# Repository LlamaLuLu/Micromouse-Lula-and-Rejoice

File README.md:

# 🐭 Micromouse Power Subsystem – EEE3088F 2025

> A modular and cost-efficient power subsystem designed for the Micromouse platform, focusing on power delivery, battery management, voltage regulation, and motor control.  
> 🔧 Built to integrate with a shared motherboard using a 2×16 pin header.

---

## 📐 Design Requirements

- Must interface with **shared motherboard via 2×16 pin header**
- All subsystems must **interoperate safely and reliably**
- Total cost must not exceed **$28.25 per student**
- Designed with **PCB production in mind** (JLCPCB compatible)

---

## ⚡ Subsystems Overview

### 1. USB-C Power Input
- **Objective**: Extract and regulate power from USB-C
- **Default Output**: 5V  
- **Target Output**: 9V
- **Approaches**:
  - Step-up converter (boost from 5V)
  - Request 9V from port using USB PD (Power Delivery) negotiation

### 2. Battery Management
- **Battery**: 3.7V 800mAh LiPo (used in micro robotics)
- **Charging Input**: 9V (from USB-C)
- **Charging Modes**:
  - Low current: **200mA**
  - High current: **(600 ± 100)mA**
- **Key Considerations**:
  - LiPo is **sensitive to overcharging**
- **Design Strategies**:
  - Use a **battery management IC**
  - Dual-mode charging circuit (selectable)
    - Separate high- and low-current paths
  - OR: Current regulation on USB-C input side that supports both modes

### 3. Power Switching & Regulation

#### 🔌 Power Switch
- Enables/disables battery output to downstream circuits

#### 🔋 Voltage Regulation
- Battery output can supply up to **400mA**
- **Approach**: Efficient voltage regulation using buck converters
- **Protection**: Optional current amplification for regulated rails

#### 🔀 External Load Switching
- Must control **2 external loads**, each up to **1A**
- **Solution**: High-current **MOSFET switching circuits**
- Current path design considers **external load values**

### 4. Components & Motor Drivers

#### 🔍 Current Sensor
- **INA219** or similar  
- Connects via **I²C**  
- Placed on high-side battery line for real-time monitoring

#### 🚗 Motor Control
- **Primary Motors**: 2 × 200mA  
- **Auxiliary Motors**: 2 × 500mA  
- Control via **dual H-bridge** motor driver (e.g., DRV8833)
- Motors driven bidirectionally using **PWM from MCU**

---

## 🧰 Production & Submission Instructions (EEE3088F)

The final PCB submission is in a zipped folder:
[Final PCB Files](./EEE3088F_PCB_Project/jlcpcb/production_files/EEE3088F_2025_Project_PCB_Files_Group_66_LNGLUL002_MTMREJ003.zip)

_ZIP File Includes:_
1. Zipped **Gerber** files (with silkscreen including group & student numbers)
2. **BOM `.csv`** file  
3. **POS/CPL `.csv`** file  
4. Screenshot of **JLCPCB BOM upload** page  
5. Screenshot of **JLCPCB Add to Cart** confirmation page  

📷 PCB Design:
- Schematic

- PCB Wiring

- JLCPCB Design (Front)

- JLCPCB Design (Back)

---

## 👨‍💻 Authors: Group 66

- **Lulama Lingela** (LNGLUL002)
- **Rejoice Matema** (MTMREJ003)

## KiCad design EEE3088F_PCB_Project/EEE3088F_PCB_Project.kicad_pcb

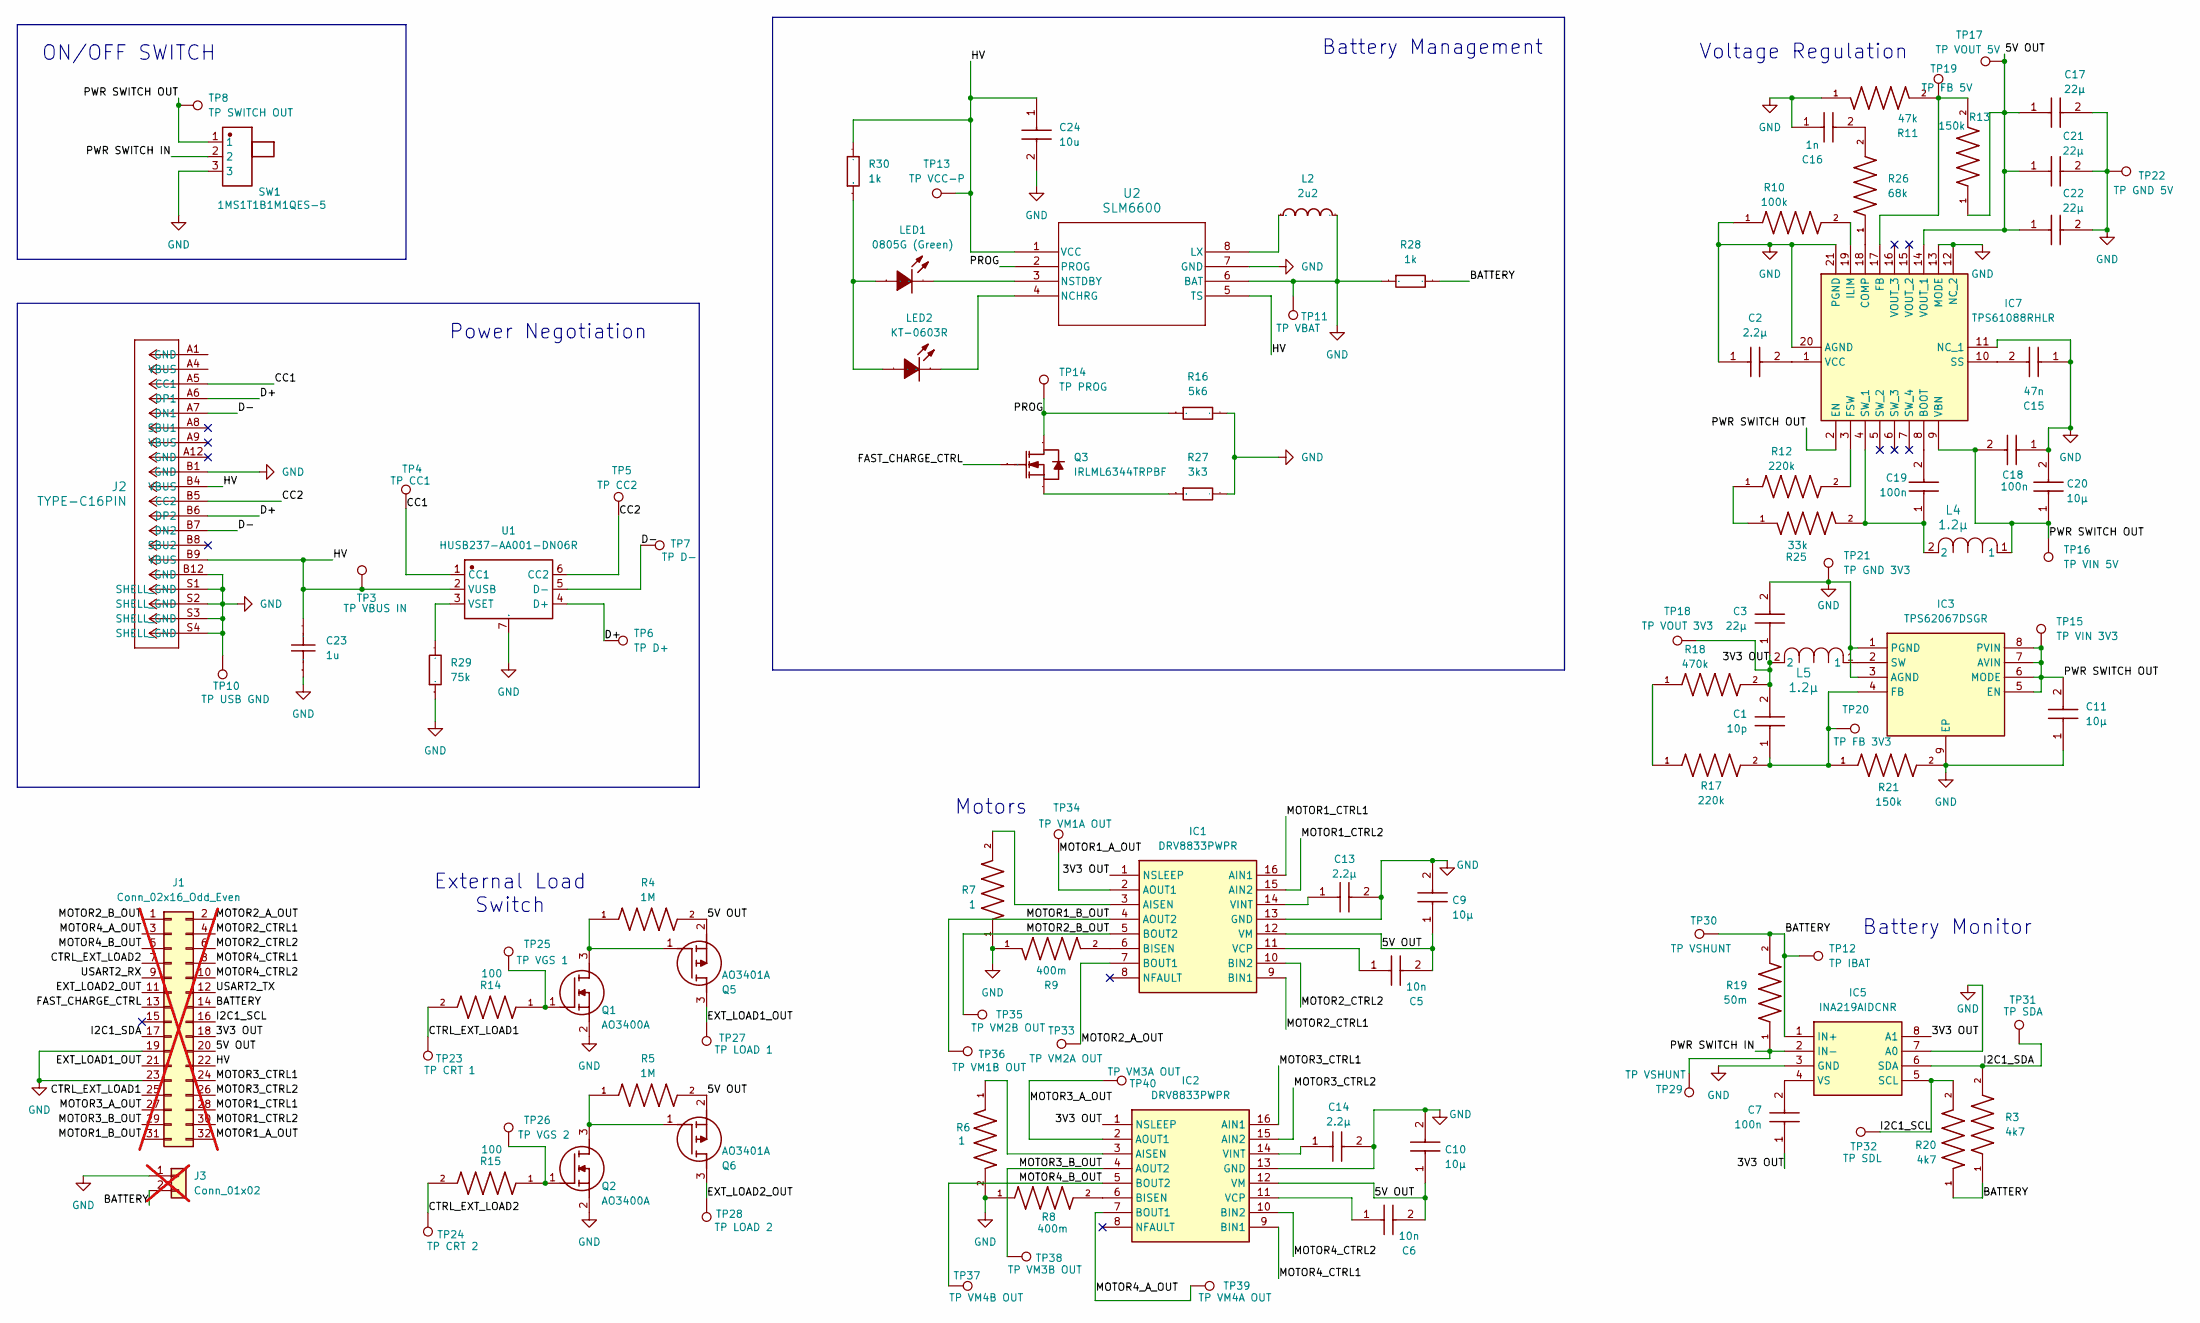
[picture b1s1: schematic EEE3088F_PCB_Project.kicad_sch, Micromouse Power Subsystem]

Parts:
C1: 10p; CAPC1608X90N; Manufacturer_Part_Number CL10C100JB8NNNC; Mouser Part Number 187-CL10C100JB8NNNC
C2, C13, C14: 2.2µ; CAPC3216X180N; Manufacturer_Part_Number CL31B225KBHNNNE; Mouser Part Number 187-CL31B225KBHNNNE
C3: 22µ; CAPC2012X140N; Manufacturer_Part_Number CL21A226MAQNNNE; Mouser Part Number 187-CL21A226MAQNNNE
C5, C6: 10n; CAPC2012X75N; Manufacturer_Part_Number CL21B103KBANNNC; Mouser Part Number 187-CL21B103KBANNNC
C7, C18, C19: 100n; CAPC3216X100N; Manufacturer_Part_Number CL31B104KBCNNNC; Mouser Part Number 187-CL31B104KBCNNNC
C9, C10, C11, C20: 10µ; CAPC3216X180N; Manufacturer_Part_Number CL31A106KBHNNNE; Mouser Part Number 187-CL31A106KBHNNNE
C15: 47n; CAPC1608X90N; Manufacturer_Part_Number CL10B473KB8NNNC; Mouser Part Number 187-CL10B473KB8NNNC
C16: 1n; CAPC3215X163N; Manufacturer_Part_Number 1206B102K202NT; Mouser Part Number 767-1206B102K202NT
C17, C21, C22: 22µ; CAPC2012X140N; Manufacturer_Part_Number CL31A226KAHNNNE; Mouser Part Number 187-CL31A226KAHNNNE
C23: 1u; C1206; Manufacturer Part CL31B105KBHNNNE; LCSC C1848
C24: 10u; CAPC3216X180N; Manufacturer_Part_Number CL31A106KBHNNNE; Mouser Part Number 187-CL31A106KBHNNNE
IC1, IC2: DRV8833PWPR; SOP65P640X120-16N; Manufacturer_Part_Number DRV8833PWPR; Mouser Part Number 595-DRV8833PWPR
IC3: TPS62067DSGR; SON50P200X200X80-9N; Manufacturer_Part_Number TPS62067DSGR; Mouser Part Number 595-TPS62067DSGR
IC5: INA219AIDCNR; SOP65P280X145-8N; Manufacturer_Part_Number INA219AIDCNR; Mouser Part Number 595-INA219AIDCNR
IC7: TPS61088RHLR; RHL_R-PVQFN-N20__1; Manufacturer_Part_Number TPS61088RHLR; Mouser Part Number 595-TPS61088RHLR
J1: Conn_02x16_Odd_Even; PinSocket_2x16_P2.54mm_Vertical; not fitted
J2: TYPE-C16PIN; CONN16_C16PIN_SHN; LCSC C393939
J3: Conn_01x02; JST_PH_S2B-PH-K_1x02_P2.00mm_Horizontal; not fitted
L2: 2u2; L0805; Manufacturer Part FHW0805UF2R2JST; LCSC C41651
L4, L5: 1.2µ; IND_FXL0420_CMT; LCSC C167204
LED1: 0805G (Green); LED0805-R-RD; Manufacturer Part KT-0805G; LCSC C2297
LED2: KT-0603R; LED0603-RD; Manufacturer Part KT-0603R; LCSC C2286
Q1, Q2: AO3400A; SOT95P280X125-3N; Manufacturer_Part_Number AO3400A; LCSC C20917
Q3: IRLML6344TRPBF; IRLML6344TRPBF_INF; Manufacturer Part IRLML6344TRPBF; LCSC C53550
Q5, Q6: AO3401A; SOT95P280X125-3N; Manufacturer_Part_Number AO3401A; LCSC C15127
R3, R20: 4k7; RESC3115X65N; PARTREV V3; LCSC C17936
R4, R5: 1M; RESC3115X65N; PARTREV V3; LCSC C17927
R6, R7: 1; RESC3115X65N; PARTREV V3; LCSC C17928
R8, R9: 400m; RESC3115X65N; PARTREV V3; LCSC C247521
R10: 100k; RESC3115X65N; PARTREV V3; LCSC C17900
R11: 47k; RESC2012X65N; PARTREV V3; LCSC C17713
R12, R17: 220k; RESC2012X65N; PARTREV V3; LCSC C17556
R13, R21: 150k; RESC2012X65N; PARTREV V3; LCSC C17470
R14, R15: 100; RESC3115X65N; PARTREV V3; LCSC C17901
R16: 5k6; R0402; Manufacturer Part 0402WGF5601TCE; LCSC C25908
R18: 470k; RESC2012X65N; PARTREV V3; LCSC C17709
R19: 50m; RESC3115X65N; PARTREV V3; LCSC C127691
R25: 33k; RESC2012X65N; PARTREV V3; LCSC C17633
R26: 68k; RESC2012X65N; PARTREV V3; LCSC C17801
R27: 3k3; R0402; Manufacturer Part 0402WGF3301TCE; LCSC C25890
R28, R30: 1k; R0402; Manufacturer Part 0402WGF1001TCE; LCSC C11702
R29: 75k; R0603; Manufacturer Part 0603WAF7502T5E; LCSC C23242
SW1: 1MS1T1B1M1QES-5; SW-TH_1MS1T1B1M1QES-5; Manufacturer Part 1MS1T1B1M1QES-5; LCSC C496154
TP3: TP VBUS IN; TestPoint_Pad_D1.5mm
TP4: TP CC1; TestPoint_Pad_D1.5mm
TP5: TP CC2; TestPoint_Pad_D1.5mm
TP6: TP D+; TestPoint_Pad_D1.5mm
TP7: TP D-; TestPoint_Pad_D1.5mm
TP8: TP SWITCH OUT; TestPoint_Pad_D1.5mm
TP10: TP USB GND; TestPoint_Pad_D1.5mm
TP11: TP VBAT; TestPoint_Pad_D1.5mm
TP12: TP IBAT; TestPoint_Pad_D1.5mm
TP13: TP VCC-P; TestPoint_Pad_D1.5mm
TP14: TP PROG; TestPoint_Pad_D1.5mm
TP15: TP VIN 3V3; TestPoint_Pad_D1.5mm
TP16: TP VIN 5V; TestPoint_Pad_D1.5mm
TP17: TP VOUT 5V; TestPoint_Pad_D1.5mm
TP18: TP VOUT 3V3; TestPoint_Pad_D1.5mm
TP19: TP FB 5V; TestPoint_Pad_D1.5mm
TP20: TP FB 3V3; TestPoint_Pad_D1.5mm
TP21: TP GND 3V3; TestPoint_Pad_D1.5mm
TP22: TP GND 5V; TestPoint_Pad_D1.5mm
TP23: TP CRT 1; TestPoint_Pad_D1.5mm
TP24: TP CRT 2; TestPoint_Pad_D1.5mm
TP25: TP VGS 1; TestPoint_Pad_D1.5mm
TP26: TP VGS 2; TestPoint_Pad_D1.5mm
TP27: TP LOAD 1; TestPoint_Pad_D1.5mm
TP28: TP LOAD 2; TestPoint_Pad_D1.5mm
TP29, TP30: TP VSHUNT; TestPoint_Pad_D1.5mm
TP31: TP SDA; TestPoint_Pad_D1.5mm
TP32: TP SDL; TestPoint_Pad_D1.5mm
TP33: TP VM2A OUT; TestPoint_Pad_D1.5mm
TP34: TP VM1A OUT; TestPoint_Pad_D1.5mm
TP35: TP VM2B OUT; TestPoint_Pad_D1.5mm
TP36: TP VM1B OUT; TestPoint_Pad_D1.5mm
TP37: TP VM4B OUT; TestPoint_Pad_D1.5mm
TP38: TP VM3B OUT; TestPoint_Pad_D1.5mm
TP39: TP VM4A OUT; TestPoint_Pad_D1.5mm
TP40: TP VM3A OUT; TestPoint_Pad_D1.5mm
U1: HUSB237-AA001-DN06R; TDFN-6_L2.0-W2.0-P0.65-TL-EP; Manufacturer Part HUSB237-AA001-DN06R; LCSC C22373734
U2: SLM6600; SOP8_4X5P1-1P27_SOI; LCSC C130316

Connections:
/3V3 OUT: C1.2, C3.1, C7.1, IC1.1 (NSLEEP), IC2.1 (NSLEEP), IC5.8 (A1), J1.18, L5.2, R18.2, TP18.1
/5V OUT: C5.2, C6.2, C9.1, C10.1, C17.1, C21.1, C22.1, IC1.12 (VM), IC2.12 (VM), IC7.14 (VOUT_1), J1.20, Q5.2 (S), Q6.2 (S), R4.2, R5.2, R13.1, TP17.1
/BATTERY: IC5.1 (IN+), J1.14, J3.2, R3.1, R19.2, R20.1, R28.2, TP12.1, TP30.1
/CC1: J2.A5 (CC1), TP4.1, U1.1 (CC1)
/CC2: J2.B5 (CC2), TP5.1, U1.6 (CC2)
/CTRL_EXT_LOAD1: J1.25, R14.2, TP23.1
/CTRL_EXT_LOAD2: J1.7, R15.2, TP24.1
/D+: J2.A6 (DP1), J2.B6 (DP2), TP6.1, U1.4 (D+)
/D-: J2.A7 (DN1), J2.B7 (DN2), TP7.1, U1.5 (D-)
/EXT_LOAD1_OUT: J1.21, Q5.3 (D), TP27.1
/EXT_LOAD2_OUT: J1.11, Q6.3 (D), TP28.1
/FAST_CHARGE_CTRL: J1.13, Q3.1 (G)
/HV: C23.2, C24.1, J1.22, J2.B4 (VBUS), J2.B9 (VBUS), R30.2, TP3.1, TP13.1, U1.2 (VUSB), U2.1 (VCC), U2.5 (TS)
/I2C1_SCL: IC5.5 (SCL), J1.16, R20.2, TP32.1
/I2C1_SDA: IC5.6 (SDA), J1.17, R3.2, TP31.1
/MOTOR1_A_OUT: IC1.2 (AOUT1), J1.32, TP34.1
/MOTOR1_B_OUT: IC1.4 (AOUT2), J1.31, TP36.1
/MOTOR1_CTRL1: IC1.16 (AIN1), J1.28
/MOTOR1_CTRL2: IC1.15 (AIN2), J1.30
/MOTOR2_A_OUT: IC1.7 (BOUT1), J1.2, TP33.1
/MOTOR2_B_OUT: IC1.5 (BOUT2), J1.1, TP35.1
/MOTOR2_CTRL1: IC1.9 (BIN1), J1.4
/MOTOR2_CTRL2: IC1.10 (BIN2), J1.6
/MOTOR3_A_OUT: IC2.2 (AOUT1), J1.27, TP40.1
/MOTOR3_B_OUT: IC2.4 (AOUT2), J1.29, TP38.1
/MOTOR3_CTRL1: IC2.16 (AIN1), J1.24
/MOTOR3_CTRL2: IC2.15 (AIN2), J1.26
/MOTOR4_A_OUT: IC2.7 (BOUT1), J1.3, TP39.1
/MOTOR4_B_OUT: IC2.5 (BOUT2), J1.5, TP37.1
/MOTOR4_CTRL1: IC2.9 (BIN1), J1.8
/MOTOR4_CTRL2: IC2.10 (BIN2), J1.10
/PROG: Q3.3 (D), R16.1, TP14.1, U2.2 (PROG)
/PWR SWITCH IN: IC5.2 (IN-), R19.1, SW1.2, TP29.1
/PWR SWITCH OUT: C11.2, C18.2, C20.1, IC3.5 (EN), IC3.6 (MODE), IC3.7 (AVIN), IC3.8 (PVIN), IC7.2 (EN), IC7.9 (VBN), L4.1, SW1.1, TP8.1, TP15.1, TP16.1
/USART2_RX: J1.9
/USART2_TX: J1.12
GND: C2.1, C3.2, C9.2, C10.2, C11.1, C13.2, C14.2, C15.1, C16.1, C17.2, C18.1, C20.2, C21.2, C22.2, C23.1, C24.2, IC1.13 (GND), IC2.13 (GND), IC3.1 (PGND), IC3.3 (AGND), IC3.9 (EP), IC5.3 (GND), IC5.7 (A0), IC7.11 (NC_1), IC7.12 (NC_2), IC7.13 (MODE), IC7.20 (AGND), IC7.21 (PGND), J1.19, J1.23, J2.B1 (GND), J2.B12 (GND), J2.S1 (SHELL_GND), J2.S2 (SHELL_GND), J2.S3 (SHELL_GND), J2.S4 (SHELL_GND), J3.1, L2.2, Q1.2 (S), Q2.2 (S), R6.2, R7.1, R8.1, R9.1, R10.1, R11.1, R16.2, R21.2, R27.2, R28.1, R29.1, SW1.3, TP10.1, TP11.1, TP21.1, TP22.1, U1.7 (GND), U2.6 (BAT), U2.7 (GND); also elsewhere on the board
unnamed: C16.2, R26.2
unnamed: IC1.3 (AISEN), R7.2
unnamed: IC1.6 (BISEN), R9.2
unnamed: C5.1, IC1.11 (VCP)
unnamed: C13.1, IC1.14 (VINT)
unnamed: IC2.3 (AISEN), R6.1
unnamed: IC2.6 (BISEN), R8.2
unnamed: C6.1, IC2.11 (VCP)
unnamed: C14.1, IC2.14 (VINT)
unnamed: C1.1, IC3.4 (FB), R17.2, R21.1, TP20.1
unnamed: IC3.2 (SW), L5.1
unnamed: C7.2, IC5.4 (VS)
unnamed: C19.2, IC7.8 (BOOT)
unnamed: IC7.18 (COMP), R26.1
unnamed: IC7.17 (FB), R11.2, R13.2, TP19.1
unnamed: IC7.3 (FSW), R12.2
unnamed: IC7.19 (ILIM), R10.2
unnamed: C15.2, IC7.10 (SS)
unnamed: C19.1, IC7.4 (SW_1), L4.2, R25.2
unnamed: C2.2, IC7.1 (VCC)
unnamed: LED1.1 (A), LED2.2 (A), R30.1
unnamed: LED1.2 (K), U2.3 (NSTDBY)
unnamed: LED2.1 (K), U2.4 (NCHRG)
unnamed: Q1.3 (D), Q5.1 (G), R4.1
unnamed: Q1.1 (G), R14.1, TP25.1
unnamed: Q2.3 (D), Q6.1 (G), R5.1
unnamed: Q2.1 (G), R15.1, TP26.1
unnamed: Q3.2 (S), R27.1
unnamed: R12.1, R25.1
unnamed: R17.1, R18.1
unnamed: R29.2, U1.3 (VSET)
unnamed: L2.1, U2.8 (LX)

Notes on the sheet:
Motors
Voltage Regulation
Battery Monitor
Battery Management
Power Negotiation
External Load Switch
ON/OFF SWITCH

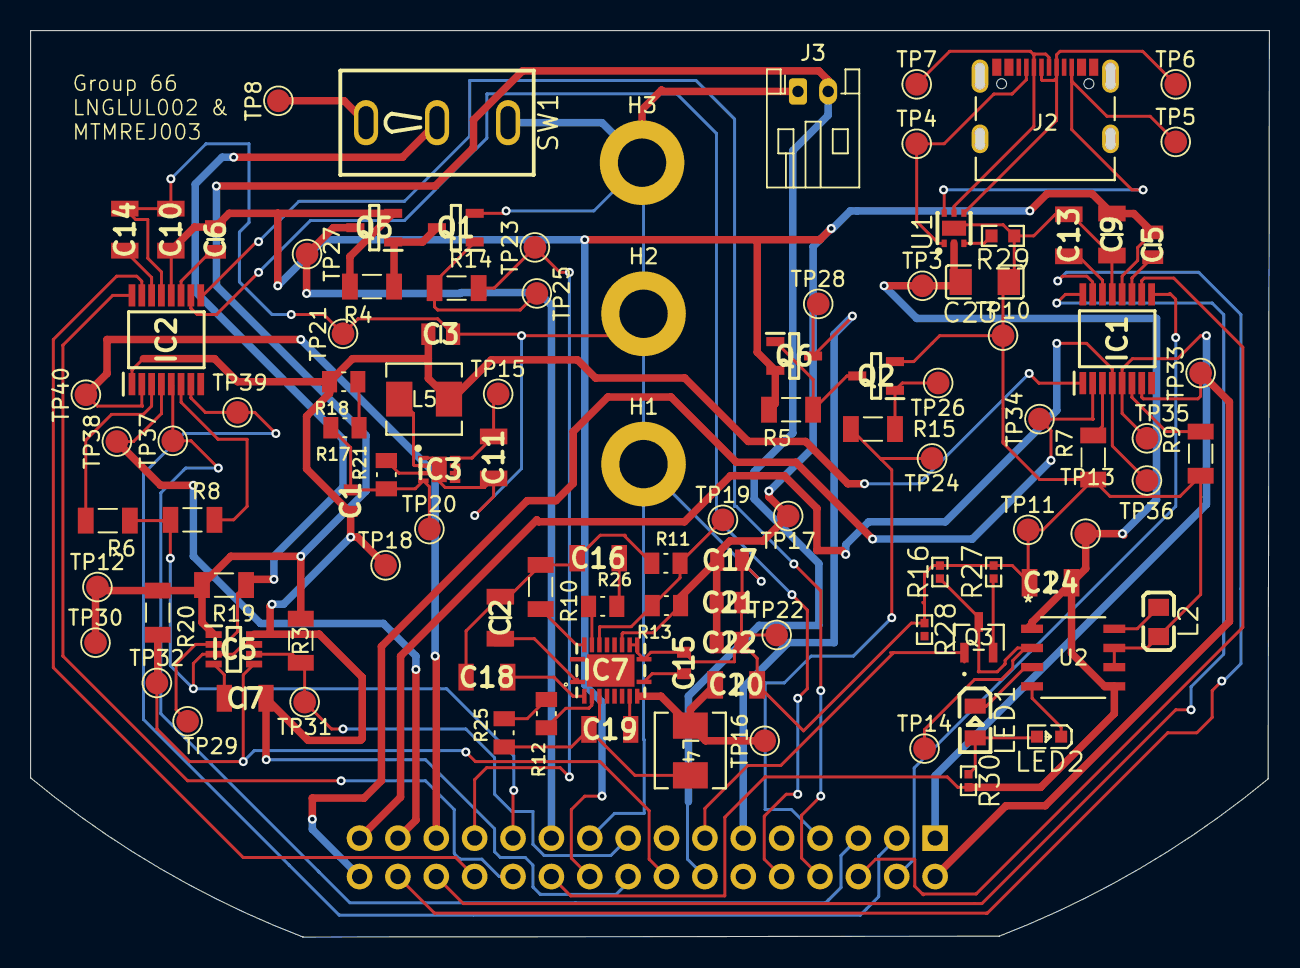
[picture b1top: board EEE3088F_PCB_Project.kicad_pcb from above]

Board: 2 copper layers, 81.4 x 59.4 mm, 107 parts (1 on the bottom side), 67 nets.

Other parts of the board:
H1, H2, H3: MountingHole_3.2mm_M3_DIN965_Pad

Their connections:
GND: H1.1, H2.1, H3.1; also elsewhere on the board

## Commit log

2025-03-24 v0
    KiCad project set up
2025-03-24 v0.1
    Lula: Essential components for my requirements imported to KiCad
2025-03-24 v0.1.1
    Lula: Rearranged position of components to make space for others
2025-03-24 v0.1.2
    Lula: Updated ICs with more compact symbols from Component Search Engine
2025-03-24 v0.1.3
    Lula: Deleted old IC file
2025-03-25 v0.1.4
    Lula: added battery datasheet
2025-03-25 v0.2
    Lula: rough battery monitor circuit done
2025-03-25 v0.2.1
    Lula: Making progress with Motor cct
2025-03-25 v0.3
    Lula: rough schematic for motors done
2025-03-25 v0.3.1
    Lula: datasheets added
2025-03-25 v0.4
    Lula: rough voltage regulator circuits done but bias resistor values not calculated
2025-03-26 v0.5
    Lula: all my rough circuits done
2025-03-26 v0.6
    Lula:
    - motors done
    - some pcb footprints added
    - imports updated
2025-03-26 v0.6.1
    Lula: starting to update battery monitor circuit
2025-03-27 v0.6.2
    Lula: all battery monitor components imported
2025-03-27 v0.6.3
    Lula: external load switch cct updated
2025-03-27 v0.7
    Lula:
    - starting with new voltage regulation cct
    - all other components updated
2025-03-27 v0.7.1
    I put another FUB file cause I saw yours late lol
2025-03-27 v0.7.2
    Lula: moved some circuits out of the way
2025-03-27 v0.7.3
    Removed the newer FUB file. Added Type-C and Im blah blah blah (Toggle Switch)
2025-03-27 v0.7.4
    Removed all my components and put updated files of them instead (FUB, SLM, 1MS, TYPE-C)
2025-03-27 v0.7.5
    Removed Type-C again and added another Type-C and IRLM
2025-03-27 v0.7.6
    Edit for previous updates: Added some components to KiCad.
    Changed some names of my sym files and added components to KiCad
2025-03-27 v0.7.7
    I have my components on the sheet. That's all I remember right now lol
2025-03-28 v0.8
    - updated voltage regulation circuit (still adjusting component values)
2025-03-28 v0.8.1
    Voltage regulator components updated
2025-03-28 v0.8.2
    Added another component
2025-03-28 v0.8.3
    A lot of stuff happened
2025-03-28 Revert "v0.8.3"
    This reverts commit e022e12157d8067f7fb354b48d193a9b7dd025b4.
2025-03-28 v0.9
    Created my circuits in KiCad
2025-03-28 v1.0
    Changed V-REG to PWR SWITCH OUT
2025-03-28 v1.1
    All circuit schematics done
2025-03-28 v1.1.1
    Making sure all changes saved
2025-03-28 v1.2
    Starting with PCB design
2025-03-28 v1.2.1
    Added the rest of my component files to the Imported Components
2025-03-28 v1.2.2
    Footprints added
2025-03-28 v1.3
    Lula: all my footprints imported and circuits grouped on PCB
2025-03-28 v1.3.1
    Most components placed on PCB
2025-03-28 v1.3.2
    Added test points to my parts of the circuit (and some)
2025-03-28 V1.3.3
    Added test points to my parts of the circuit
2025-03-28 v1.3.4
    test points added
2025-03-28 V1.4
    FAILED
2025-03-28 Revert "V1.4"
    This reverts commit e5222738783ebac659cce19e32834096aa7270f5.
2025-03-28 Revert "v1.3.4"
    This reverts commit 31f4348740902cc06db09578befa2d9091b6bdd9.
2025-03-28 Revert "V1.3.3"
    This reverts commit 82317ec0dd0d0933929f69b93ecb048d09c96738.
2025-03-28 V1.4.1
    last minute things
2025-03-28 v1.4.2
    saving last minute changes
2025-03-28 v1.4.1
    actually want to go back to version before wiring
2025-03-28 v1.4
    new start - setup proper edge cuts
2025-03-28 v1.4.3
    switching branches
2025-03-28 v1.4.1
    - all footprints assigned
    - components neatly placed on PCB
2025-03-28 v1.4.2
    - inner shape removed from pcb
2025-03-28 v1.5.1
    - tried adding wiring but hit edge
2025-03-28 v1.5.2
    saving changes
2025-03-28 v1.5.3
    updating changes
2025-03-28 Revert "v1.5.3"
    This reverts commit 1de1613c8c6e3748df64e612ca9ed2fbbcde8f2e.
2025-03-28 Revert "v1.5.2"
    This reverts commit 51cb19e0555e6a1b099874e78e333fc85f141e8d.
2025-03-28 Revert "v1.5.1"
    This reverts commit 95b0540061ed2b4f31283696902dc0dbdf64c944.
2025-03-28 v1.4.3
    - added design rules & keep out area before wiring
2025-03-28 v1.5
    - wiring done!
2025-03-28 v1.5.0
    - added images of pcb design
2025-03-28 v1.5.4
    - added LCSC number for all component properties
2025-03-28 v2.0
    IT'S DONE!!!
2025-03-29 v2.0.1
    - added all jclpcb images
2025-03-29 v2.0.2
    checking updates
2025-03-29 v.1.4.4
    - updated PCB shape
2025-03-29 v1.5
    - wiring done but at what cost
2025-04-04 Revert "v1.5"
    This reverts commit 904848d5ff92434ff16791d24f5233f2f40037b0.
2025-04-04 V1.4.5
    - assigned LCSC numbers to components
2025-04-04 v1.5
    - making progress with manual wiring
2025-04-04 v1.5.1
    - made more progress with wiring
2025-04-04 v1.5.2
    - resolved 'no connection' issue in battery management
2025-04-04 v1.5.3
    - started adding vias
    - making more progress with wiring
2025-04-05 v1.5.4
    - need to finish wiring to main connector
2025-04-05 v1.5.5
    - just need to connect motor pins
2025-04-05 v1.5.6
    - 4 more main connectors to go
2025-04-05 v1.6
    - all wiring done!
2025-04-05 v1.6.1
    - double checked LCSC numbers
2025-04-05 v1.6.2
    - final adjustments to pcb done
2025-04-05 v1.6.3
    - adjusted schematic layout
2025-04-05 v1.7
    - generated gerber files, BOM, CPL
2025-04-05 V2.0
    - finished JLCPCB process
2025-04-05 v2.0.1
    - saving all changes
2025-04-20 v2.1
    - renamed relevant files for github readme
